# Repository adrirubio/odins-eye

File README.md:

# Odin's Eye

**Full Design Process**: [Blueprint Project](https://blueprint.hackclub.com/projects/413)

A compact speed detection system using a Raspberry Pi and a TF-Luna LiDAR sensor monitors vehicles in real time. When a vehicle is detected passing by, the system measures its speed and triggers the Raspberry Pi Camera Module 3 to capture an image.

Captured images are processed locally on a Raspberry Pi Zero 2 W, where the system identifies the vehicle and, when applicable, extracts license plate information. With built-in Wi-Fi connectivity, the unit wirelessly transmits speed data and image results directly to your phone. The entire system is designed to operate autonomously, combining precise sensing, on-device image analysis, and seamless wireless communication in a compact DIY build.

## Features

- **Vehicle Speed Detection:** Real-time speed measurement using a TF-Luna LiDAR sensor
- **Automatic Photo Capture:** Raspberry Pi Camera Module 3 captures an image when a vehicle passes
- **On-Device Processing:** Raspberry Pi Zero 2 W analyzes captured images locally
- **Vehicle Recognition:** Detects vehicles within the captured image
- **License Plate Detection:** Extracts license plate information when a car is detected
- **Wireless Notifications:** Sends captured data and images directly to your phone over WiFi
- **OLED Display:** Shows detected speed and system status directly on the device
- **Autonomous Operation:** Runs continuously without manual interaction
- **Compact DIY Design:** Designed as a small, self-contained monitoring system

## Hardware/BOM

| Component | Qty | Type |
|-----------|-----|------|
| Raspberry Pi Zero 2 W | 1 | Controller |
| Raspberry Pi Camera Module 3 | 1 | Camera Module |
| TF-Luna LiDAR Sensor | 1 | LiDAR Sensor |
| 0.95-inch OLED Display | 1 | Display |
| MPU6050 IMU | 1 | Sensor |
| microSD Card (32GB) | 1 | Storage |
| Custom Carrier PCB | 1 | PCB |
| Custom 3D Printed Case | 1 | Enclosure |
| Power Bank | 1 | Power |
| USB-A to USB-C Cable | 1 | Cable |
| Universal Tripod | 1 | Mount |
| Green LED Power Indicator | 1 | Indicator |
| Mounting Hardware (Assorted Screws) | 1 | Hardware |

## CAD Screenshots

| CAD Assembly (Front View)| CAD Assembly (Back View) |
|-------------------------------|-------------------------------|
|  |  |

| 3D Case (Side View) | 3D Case (Side View) |
|----------------------|---------------------|
|  |  |

## PCB Screenshots

| PCB Layout |
|-------------------------------|
|  |

| PCB 3D View (Front) | PCB 3D View (Back) |
|----------------------|---------------------|
|  |  |

## Usage
Place the system facing the road and use the built-in gyroscope to help align the device at the correct angle for accurate measurements. The TF-Luna LiDAR sensor detects passing vehicles and calculates their speed, triggering the camera to capture an image as a vehicle passes. The Raspberry Pi then processes the image to detect the vehicle and extract the license plate if possible, sending the results to your phone over WiFi. The detected speed and system status are also displayed on the integrated OLED screen, allowing you to quickly view results directly on the device.

## Odins Eye In Action

| Complete Assembly |
|-------------------------------|
|  |

| Complete Assembly (Front View)| Complete Assembly (Front View) |
|-------------------------------|-------------------------------|
|  |  |

| Complete Assembly (Top View)| Complete Assembly (Side View) |
|-----------------------------|-------------------------------|
|  |  |

| Complete Assembly (Back View)| Complete Assembly (Back View) |
|------------------------------|-------------------------------|
|  |  |

### Odins Eye Demo
<a href="https://github.com/adrirubio/odins-eye/raw/main/demo/video/odins-eye-demo.mp4">Click here to download the demo video (MP4)</a>

### YouTube Demo
[Watch the demo on YouTube](https://youtu.be/cNV2ZcgS8Qw)

## Running on the Pi

The firmware lives in `firmware/`. Two entry points:

- `odins_eye_speed_monitor.py` — the live detector (TF-Luna sampling, gyro calibration, camera trigger, capture metadata).
- `odins_eye_dashboard_server.py` — a small HTTP server that serves the latest captures at `http://<pi-ip>:8080`.

### One-time setup on the Pi

```bash
sudo apt install python3-pil python3-smbus2 rpicam-apps
git clone https://github.com/adrirubio/odins-eye.git ~/Documents/odins-eye
sudo bash ~/Documents/odins-eye/firmware/systemd/install.sh
```

The install script copies the systemd units into `/etc/systemd/system/`, enables them, and starts both services. After a reboot, both come up automatically.

### Manual run for roadside testing

When you want the gyro calibration prompt and live burst logs in your terminal:

```bash
sudo systemctl stop odins-eye-detector
bash ~/Documents/odins-eye/firmware/odins_eye_start.sh
```

Ctrl-C stops both detector and dashboard. To return to autostart mode:

```bash
sudo systemctl start odins-eye-detector
```

### Useful commands

```bash
systemctl status odins-eye-detector
systemctl status odins-eye-dashboard
journalctl -u odins-eye-detector -f          # live detector log
journalctl -u odins-eye-dashboard -f         # live dashboard log
```

## License

MIT License

---

> GitHub [@adrirubio](https://github.com/adrirubio) &nbsp;&middot;&nbsp;

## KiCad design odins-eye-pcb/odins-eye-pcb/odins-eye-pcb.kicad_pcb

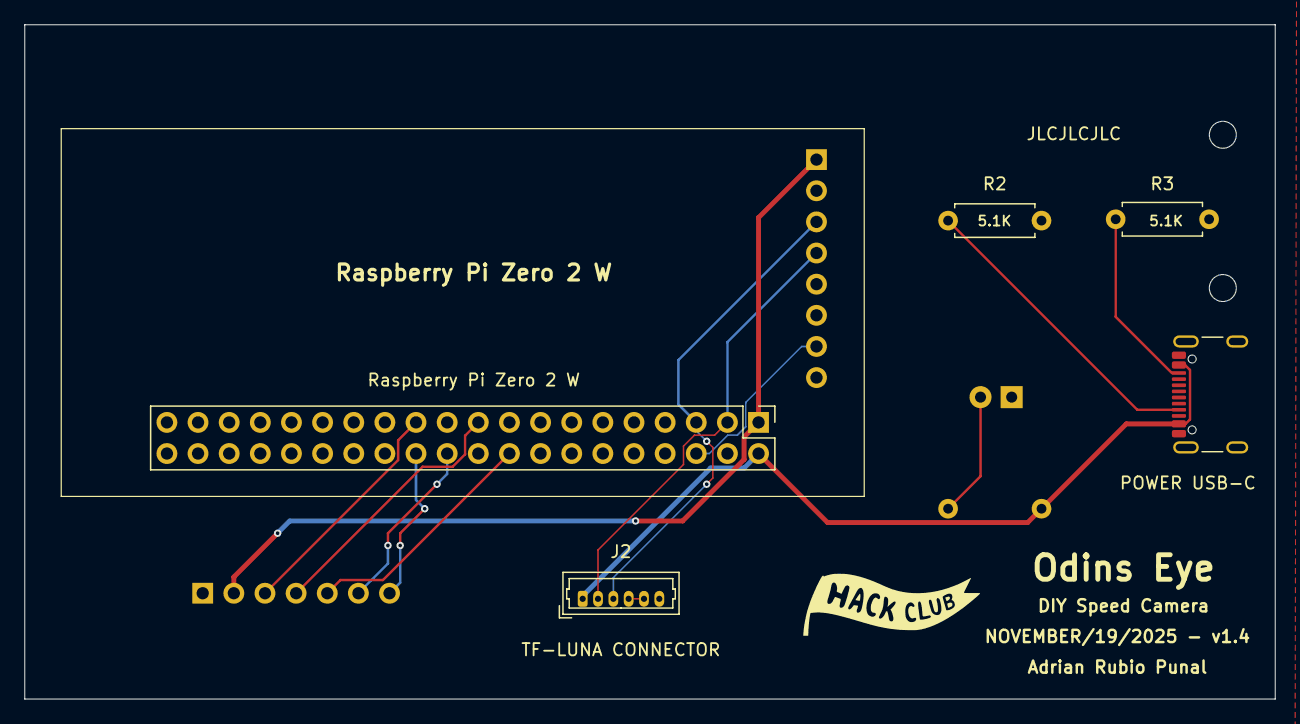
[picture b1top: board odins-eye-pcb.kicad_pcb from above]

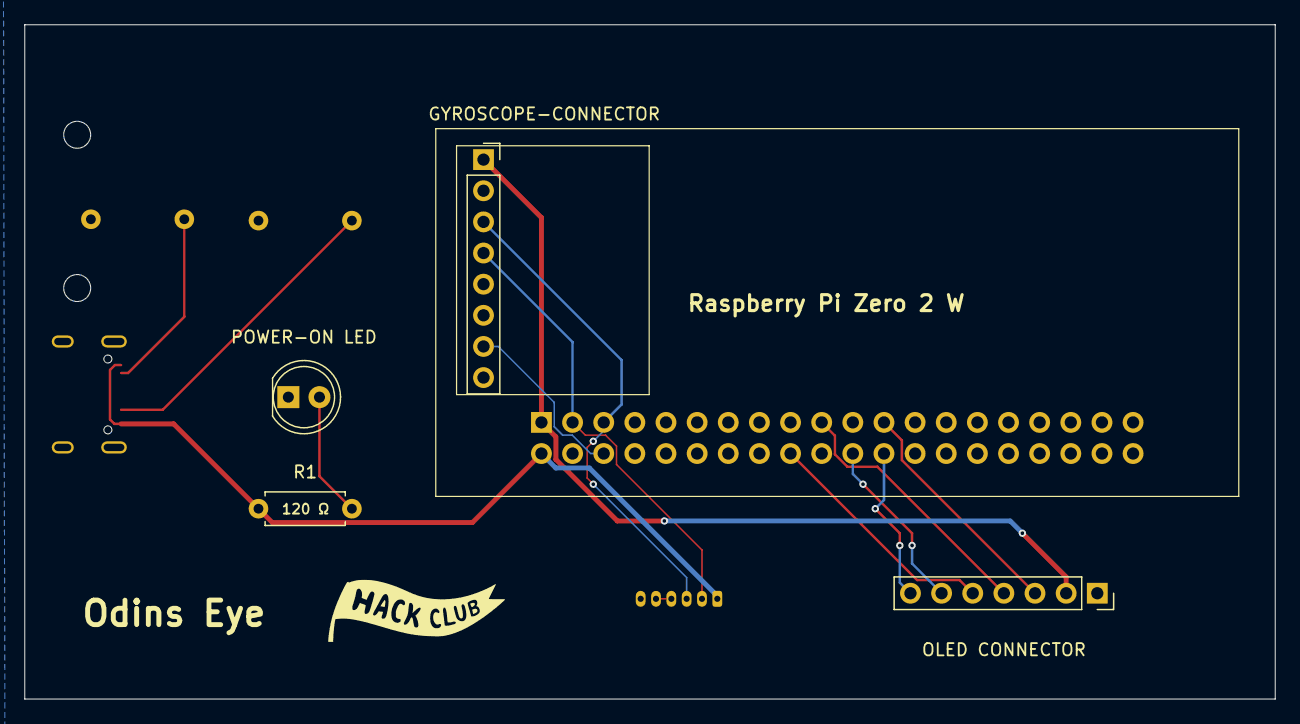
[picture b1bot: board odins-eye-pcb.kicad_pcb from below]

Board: 4 copper layers, 102.0 x 55.0 mm, 9 parts (4 on the bottom side), 13 nets.

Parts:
J2: TF-LUNA CONNECTOR; Molex_PicoBlade_53047-0610_1x06_P1.25mm_Vertical
J3: POWER USB-C; USB_C_Receptacle_GCT_USB4105-xx-A_16P_TopMnt_Horizontal
J4: GYROSCOPE-CONNECTOR; PinSocket_1x08_P2.54mm_Vertical
OLED CONNECTOR: Conn_01x07_Pin; PinSocket_1x07_P2.54mm_Vertical
POWER-ON LED: LED; LED_D5.0mm
R1: 120; R_Axial_DIN0207_L6.3mm_D2.5mm_P7.62mm_Horizontal
R2, R3: 5.1K; R_Axial_DIN0207_L6.3mm_D2.5mm_P7.62mm_Horizontal
Raspberry Pi Zero 2 W: Raspberry Pi Zero 2 W Header; PinSocket_2x20_P2.54mm_Vertical

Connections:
+3V3: J4.1, OLED CONNECTOR.2, Raspberry Pi Zero 2 W.1 (3V3)
+5V: J2.1, J3.A4 (VBUS), J3.A9 (VBUS), J3.B4 (VBUS), J3.B9 (VBUS), R1.1, Raspberry Pi Zero 2 W.2 (5V)
/CS: OLED CONNECTOR.7, Raspberry Pi Zero 2 W.24 (CE0)
/DC: OLED CONNECTOR.6, Raspberry Pi Zero 2 W.22 (GPIO25)
/MOSI: OLED CONNECTOR.4, Raspberry Pi Zero 2 W.19 (MOSI)
/RST: OLED CONNECTOR.5, Raspberry Pi Zero 2 W.18 (GPIO24)
/SCK: OLED CONNECTOR.3, Raspberry Pi Zero 2 W.23 (SCLK)
/SCL: J2.3, J4.3, Raspberry Pi Zero 2 W.5 (SCL1)
/SDA: J2.2, J4.4, Raspberry Pi Zero 2 W.3 (SDA1)
GND: J2.4, J2.5, J3.A1 (GND), J3.A12 (GND), J3.B1 (GND), J3.B12 (GND), J3.S1 (SHIELD), J4.2, J4.7, OLED CONNECTOR.1, POWER-ON LED.1 (K), R2.2, R3.2, Raspberry Pi Zero 2 W.6 (GND)
unnamed: POWER-ON LED.2 (A), R1.2
unnamed: J3.A5 (CC1), R2.1
unnamed: J3.B5 (CC2), R3.1

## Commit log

2025-10-12 Initial bom.csv
2025-10-19 Add speed calculation code
2025-11-19 Add KiCad files
2025-11-26 Add test TF Luna distance code
2025-11-27 Add odins-eye v1.1
2025-12-06 Update arduino code
2025-12-08 Project enclosure
2025-12-16 Update 3D printed case
2025-12-16 Push finished 3d case
2025-12-16 Add updated pcb with corresponding gerber
2025-12-16 Made small, final change to case
2025-12-17 Add small changes
2025-12-20 Small changes
2025-12-31 Update 3D case
2026-01-02 Changes to the 3D case
2026-01-11 Push STL files for the finished 3D case
2026-01-20 Add PCB v1.5
2026-03-01 Add STEP files
2026-03-01 Clean pcb folder
2026-03-03 Begin readme
2026-03-04 Continue work on README
2026-05-03 Add speed detection code and update readme with finished project images
2026-05-12 Upload updated speed detetion and dashboard code
2026-05-12 Upload demo video and finish README with youtube and MP4 video links
2026-05-13 Add image of the finished complete assembly to README
2026-05-14 Change video link in README
